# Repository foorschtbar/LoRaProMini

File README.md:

# LoRaProMini - A low power LoRaWAN Node

[

](https://github.com/foorschtbar/LoRaProMini)

A LoRaWAN sensor node, based on ATmega328P MCU (Arduino Pro Mini) and RFM95W/SX1276 LoRa Transceiver.

The module can be used:

- Collect various climate values with environmental sensors. See [Environmental (Weather/Clima) Sensor](#environmental-weatherclima-sensor)
- Tell if the letter carrier has put new letters in your mailbox. See [Mailbox Monitor](#mailbox-monitor)
- Notify if someone rang the doorbell
- Act a wirless button
- and many more...

## Features

- Deep sleep MCU and sensors between data transmissions
- Two interrupt inputs could use to wake up the MCU and sensors from deep sleep
- Confirmend und unconfirmend data up messages
- Ultra low power consumption. Under 10μA with all features and sensors
- Power input 3.5-6V:
  - Battery (Li-Ion or Li-SOCl2 works fine)
  - Battery with solar charger
- Sensor support
  - Bosch BME280 (humidity, barometric pressure and ambient temperature)
  - Maxim DS18B20(+)/DS18S20(+)/DS1822 1-Wire temperature sensor

### Warning

LoRaProMini does not take care of the compliance with the duty cycle limitation. Please select only transmission intervals that are within the legal limits (1%/0.1%). Please also note that the interrupt inputs may cause additional transmissions if this function is activated.

### PCB Ordering

:point_up: I still have a few PCBs left. If you are interested please contact me. Contact details can be found here: https://github.com/foorschtbar or visit my Tindie store:

## Example Applications

### Environmental (Weather/Clima) Sensor

- Download [Radiation Shield STL](https://www.prusaprinters.org/prints/73421-radiation-shield-for-diy-weather-station)
- Buy [Waterproof LED Solar Light](https://s.click.aliexpress.com/e/_9AKunB)

### Mailbox Monitor

- Download [Case STL](https://www.prusaprinters.org/prints/132941-case-for-lorawan-mailbox-monitor-lorapromini)
- Buy [Normally Opened Reed Switches](https://s.click.aliexpress.com/e/_AU1hN3)

## More pics

## The Things Stack configuration

- LoRaWAN version `MAC V1.0.3`

## How to use

1. Manufacture the PCB. Here you find the [Gerber](pcb) files
1. Assemble the PCB. Here you find the [Bill of Materials](https://foorschtbar.github.io/LoRaProMini/pcb/bom/ibom.html) (BOM)
   - **Attention:** The current version (v3.1) of the PCB has no ISP header! A pre-burned Atmega328P must be installed. I got one from an Arduino Pro Mini Board (3.3V 8 Mhz), because a completely assembled Arduino is cheaper than a single chip
1. Flash config firmware (See [How to flash](#how-to-flash))
1. Start voltage calibration from menu
1. Start configuration builder [Configuration Builder](https://foorschtbar.github.io/LoRaProMini/configbuilder)
1. Measure the voltage with a multimeter
1. Insert multimeter voltage and the analog value in the Volts-per-bit (VPB) calculator to get VPB factor.
1. If u have a adjustable power supply, try different voltages to find best factor. Warning: The maximum voltage is 6 Volt
1. Fill out the other fields like activation methode, session keys and EUIs
1. Write configuration to EEPROM using configuration menu
1. Check written configuration via configuration menu
1. Flash debug or release firmware (See [How to flash](#how-to-flash))
1. Finish

## How to flash

```
avrdude-F -v -c arduino -p atmega328p -P <COM PORT> -b 57600 -D -U flash:w:<FIRMWARE FILE>:i
```

Example:

```
avrdude -F -v -c arduino -p atmega328p -P COM4 -b 57600 -D -U flash:w:firmware_1.0_config.hex:i
```

## Firmware Changelog

### Version 2.7

- Fixed a problem of resetting the interrupt trigger too early.

### Version 2.6

- Second attempt to solve the unnecessary delay due to the duty cycle limitation. Overflow of timer0 freezes the MCU after around 20 transmissions.

### Version 2.5

- Fixed problem with duty cycle limitation
- Fixed MCU deepsleep inaccuracy

### Version 2.4

- An external interrupt during a transmission terminates the transmission and starts a new transmission.
- Enabled Link Check Mode

### Version 2.3

- Fixed Typo

### Version 2.2

- An additional send delay between 0 and 20s has been added to avoid overlaps between different nodes with exactly the same send interval
- Some flash memory optimizations

### Version 2.1

- Improved (debug) logging to serial output
- BME sends -127°C (link DS18x) if no sensor was found

### Version 2.0

- Added wake up trough interrupt pins
- Added option for disable interrupt pins
- Added option for confirmed uplink
- Changed LoRaWAN data up message
  - Added state of interrupt pins
  - Combined major and minor version byte into a single byte (4 bits for major and 4 bits for minor)

### Version 1.1

- Only for testing CI Pipeline

### Version 1.0

- Initial Version

## PCB Changelog

### Version 3.2

- Fixed C7 (Replaced 10uF with 100nF)

### Version 3.1

- Added white field to specify the Node ID

### Version 3.0

- Removed Arduino Pro Mini Dauther PCB
- Added ATMEGA328P direct to the PCB
- Added pins for unused GPIOs
- Added D2 and D3 with Pulldowns and connector as external interrupts (need FW v2.0 or higher)

### Version 2.2

- Added RST pin to connector for programming

### Version 2.1

- Added connector for programming

### Version 2.0

- Smaller PCB
- Rounded Edges
- Fixed issue with DS18x onboard pin mapping

### Version 1.0

- Initial PCB

## TTS Payload Formatter (formerly TTN Payload Decoder)

```javascript
function decodeUplink(input) {
  var bytes = input.bytes;

  var itrTrigger = (bytes[0] & 0x1) !== 0; // Message was triggered from interrupt (bit 0)
  var itr0 = (bytes[0] & 0x2) !== 0; // Interrupt 0 (bit 1)
  var itr1 = (bytes[0] & 0x4) !== 0; // Interrupt 1 (bit 2)
  var bat = (bytes[1] << 8) | bytes[2]; // Battery
  var fwversion = (bytes[3] >> 4) + "." + (bytes[3] & 0xf); // Firmware version
  var temp1 = (bytes[4] & 0x80 ? 0xffff << 16 : 0) | (bytes[4] << 8) | bytes[5]; // BME Temperature
  var humi1 = (bytes[6] << 8) | bytes[7]; // BME Humidity
  var press1 = (bytes[8] << 8) | bytes[9]; // BME Pressure
  var temp2 =
    (bytes[10] & 0x80 ? 0xffff << 16 : 0) | (bytes[10] << 8) | bytes[11]; // DS18x Temperature

  var mbStatus = "UNKNOWN";
  if (itr0) {
    mbStatus = "FULL";
  } else if (itr1) {
    mbStatus = "EMPTY";
  }

  return {
    data: {
      interrupts: {
        itr0: itr0,
        itr1: itr1,
        itrTrigger: itrTrigger,
      },
      extra: {
        mbStatus: mbStatus,
        mbChanged: itrTrigger,
      },
      fwversion: fwversion,
      bme: {
        temperature: temp1 / 100,
        humidity: humi1 / 100,
        pressure: press1,
      },
      ds18x: {
        temperature: temp2 / 100,
      },
      battery: bat / 100,
    },
    warnings: [],
    errors: [],
  };
}
```

## ToDo

- [ ] Go to sleep immediately when voltage is too low
- [ ] Multi point calibration for battery voltage
- [ ] Set ADR (On/Off)
- [ ] Set SF (7-12)
- [ ] Allow change of NetID
- [x] Add wake up trough interrupt pins
- [x] Move Major- and Minorversion byte to single byte. 4 bits for major and 4 bits for minor.
- [x] Add option for Confirmed Uplink to config
- [x] Add CI/CD pipeline to build firmware
- [x] Rewirte VBP calculator in Configuration Builder
- [x] Move config to EEPROM
- [x] Added special firmware to change configs
- [x] Build HTML/JS Interface to build configs
- [x] Add CRC32 check
- [x] Test ABP
- [x] Test OTAA
- [x] Deploy config tool via GitHub Pages
- [x] Fix problem when checksum in pastend config had zeros O.o
- [x] Add random EUI generator button to config tool
- [x] Parse config string to GUI fields

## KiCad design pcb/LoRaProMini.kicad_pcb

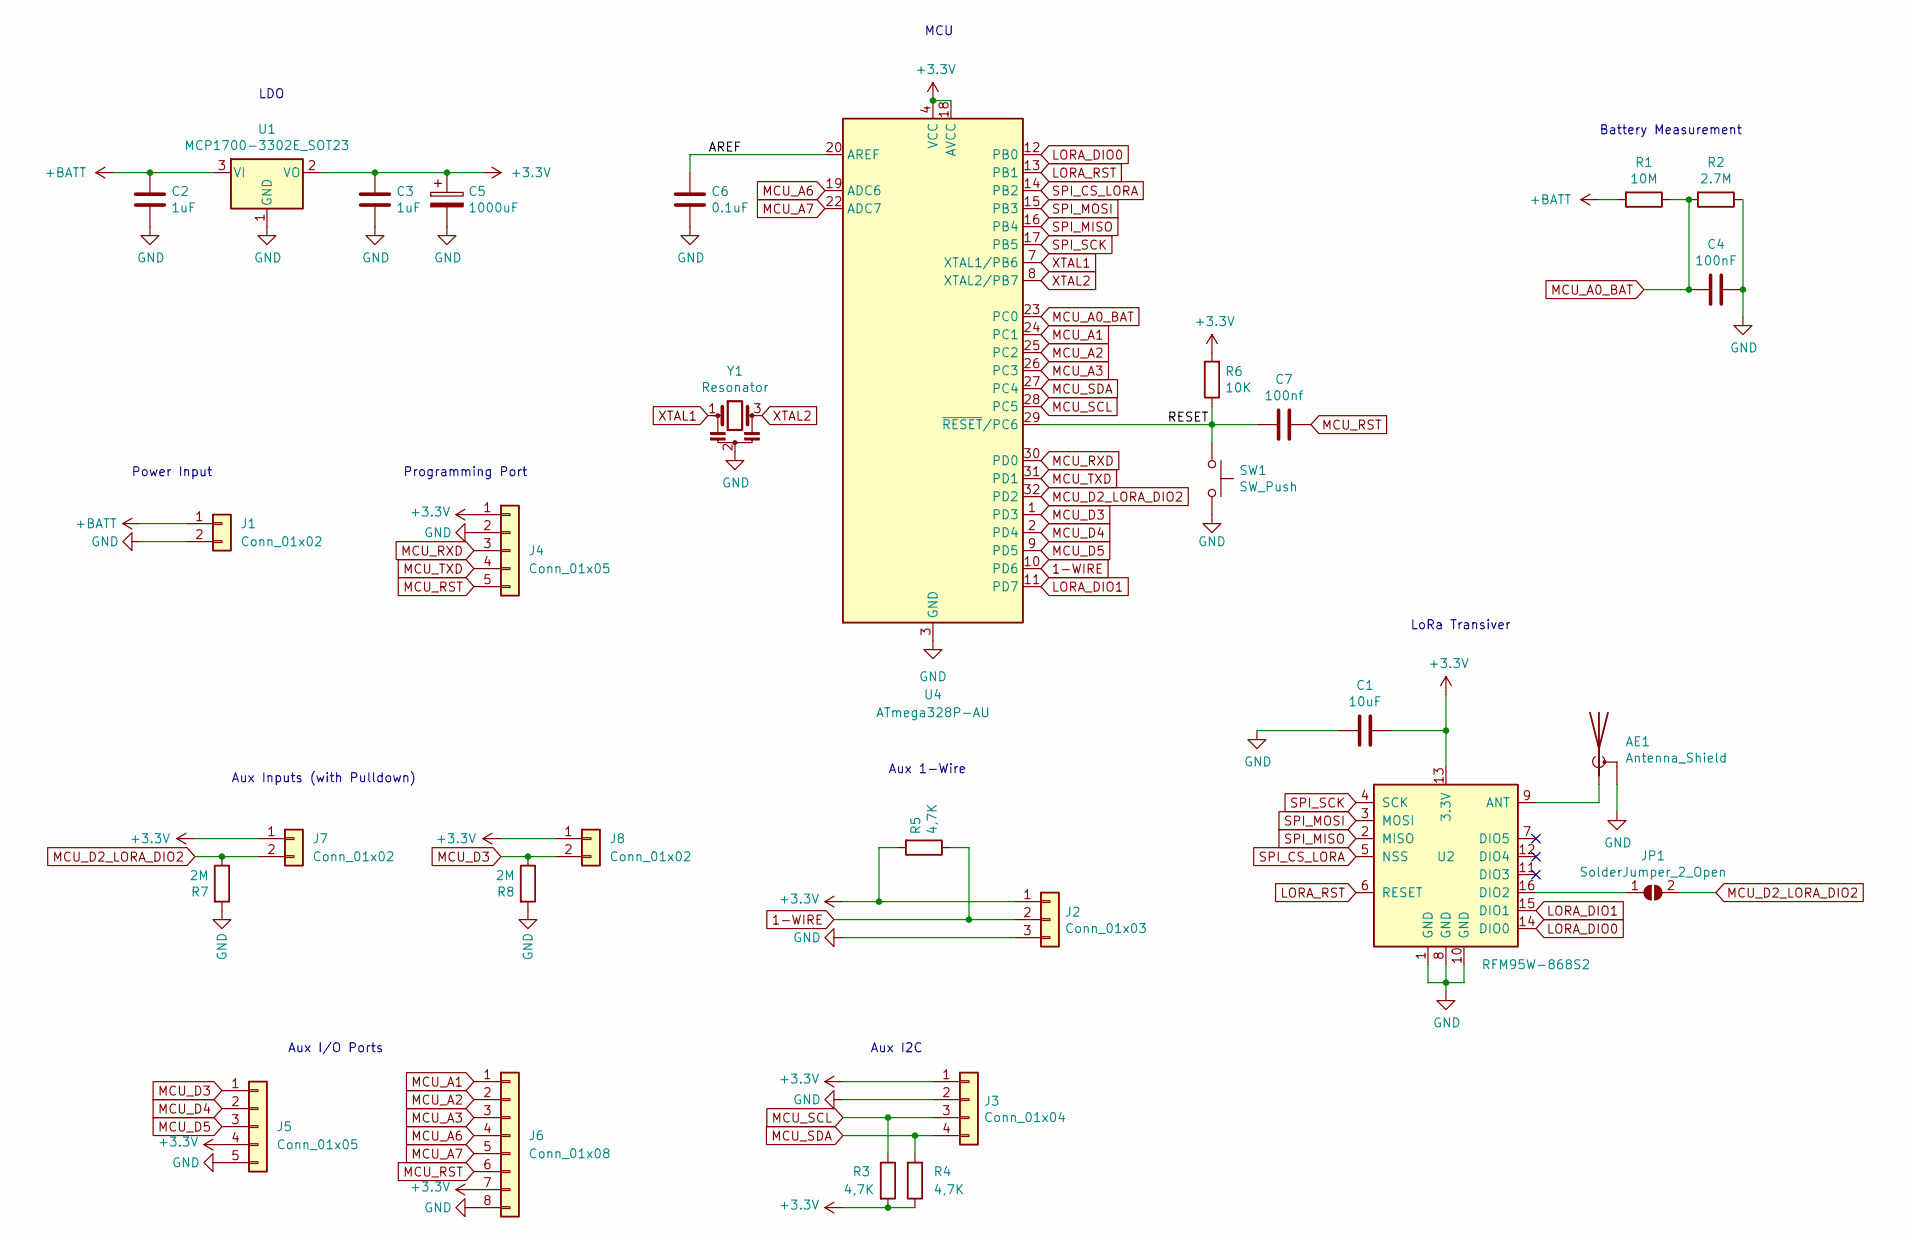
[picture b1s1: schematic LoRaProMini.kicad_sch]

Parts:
AE1: Antenna_Shield; Antenna_SMA_uFL
C1: 10uF; C_0805_2012Metric_Pad1.18x1.45mm_HandSolder
C2, C3: 1uF; C_0805_2012Metric_Pad1.18x1.45mm_HandSolder
C4: 100nF; C_0805_2012Metric_Pad1.18x1.45mm_HandSolder
C5: 1000uF; CP_EIA-7343-43_Kemet-X_Pad2.25x2.55mm_HandSolder
C6: 0.1uF; C_0805_2012Metric_Pad1.18x1.45mm_HandSolder
C7: 100nf; C_0805_2012Metric_Pad1.18x1.45mm_HandSolder
J1, J7, J8: Conn_01x02; JST_PH_B2B-PH-K_1x02_P2.00mm_Vertical
J2: Conn_01x03; JST_PH_B3B-PH-K_1x03_P2.00mm_Vertical
J3: Conn_01x04; JST_PH_B4B-PH-K_1x04_P2.00mm_Vertical
J4: Conn_01x05; PinHeader_1x05_P2.54mm_Vertical
J5: Conn_01x05; Holes_1x05_P2.54mm
J6: Conn_01x08; Holes_1x08_P2.54mm
JP1: SolderJumper_2_Open; SolderJumper-2_P1.3mm_Open_TrianglePad1.0x1.5mm
R1: 10M; R_0805_2012Metric_Pad1.20x1.40mm_HandSolder
R2: 2.7M; R_0805_2012Metric_Pad1.20x1.40mm_HandSolder
R3, R4, R5: 4,7K; R_0805_2012Metric_Pad1.20x1.40mm_HandSolder
R6: 10K; R_0805_2012Metric_Pad1.20x1.40mm_HandSolder
R7, R8: 2M; R_0805_2012Metric_Pad1.20x1.40mm_HandSolder
SW1: SW_Push; SW_SPST_CK_RS282G05A3
U1: MCP1700-3302E_SOT23; SOT-23
U2: RFM95W-868S2; HOPERF_RFM9XW_SMD
U4: ATmega328P-AU; TQFP-32_7x7mm_P0.8mm
Y1: Resonator; Resonator_SMD_Murata_CSTxExxV-3Pin_3.0x1.1mm

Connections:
1-WIRE: J2.2, R5.1, U4.10 (PD6)
+3.3V: C1.1, C3.1, C5.1, J2.1, J3.1, J4.1, J5.4, J6.7, J7.1, J8.1, R3.2, R4.1, R5.2, R6.2, U1.2 (VO), U2.13 (3.3V), U4.4 (VCC), U4.6 (VCC), U4.18 (AVCC)
+BATT: C2.1, J1.1, R1.2, U1.3 (VI)
/AREF: C6.1, U4.20 (AREF)
/RESET: C7.2, R6.1, SW1.1, U4.29 (~RESET/PC6)
GND: AE1.2 (Shield), C1.2, C2.2, C3.2, C4.1, C5.2, C6.2, J1.2, J2.3, J3.2, J4.2, J5.5, J6.8, R2.1, R7.2, R8.2, SW1.2, U1.1 (GND), U2.1 (GND), U2.8 (GND), U2.10 (GND), U4.3 (GND), U4.5 (GND), U4.21 (GND), Y1.2
LORA_DIO0: U2.14 (DIO0), U4.12 (PB0)
LORA_DIO1: U2.15 (DIO1), U4.11 (PD7)
LORA_RST: U2.6 (RESET), U4.13 (PB1)
MCU_A0_BAT: C4.2, R1.1, R2.2, U4.23 (PC0)
MCU_A1: J6.1, U4.24 (PC1)
MCU_A2: J6.2, U4.25 (PC2)
MCU_A3: J6.3, U4.26 (PC3)
MCU_A6: J6.4, U4.19 (ADC6)
MCU_A7: J6.5, U4.22 (ADC7)
MCU_D2_LORA_DIO2: J7.2, JP1.2 (B), R7.1, U4.32 (PD2)
MCU_D3: J5.1, J8.2, R8.1, U4.1 (PD3)
MCU_D4: J5.2, U4.2 (PD4)
MCU_D5: J5.3, U4.9 (PD5)
MCU_RST: C7.1, J4.5, J6.6
MCU_RXD: J4.3, U4.30 (PD0)
MCU_SCL: J3.3, R3.1, U4.28 (PC5)
MCU_SDA: J3.4, R4.2, U4.27 (PC4)
MCU_TXD: J4.4, U4.31 (PD1)
unnamed: AE1.1 (A), U2.9 (ANT)
unnamed: JP1.1 (A), U2.16 (DIO2)
SPI_CS_LORA: U2.5 (NSS), U4.14 (PB2)
SPI_MISO: U2.2 (MISO), U4.16 (PB4)
SPI_MOSI: U2.3 (MOSI), U4.15 (PB3)
SPI_SCK: U2.4 (SCK), U4.17 (PB5)
XTAL1: U4.7 (XTAL1/PB6), Y1.1
XTAL2: U4.8 (XTAL2/PB7), Y1.3

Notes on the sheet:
Aux 1-Wire
Aux I/O Ports
LDO
MCU
Power Input
Battery Measurement
Aux I2C
Aux Inputs (with Pulldown)
Programming Port
LoRa Transiver

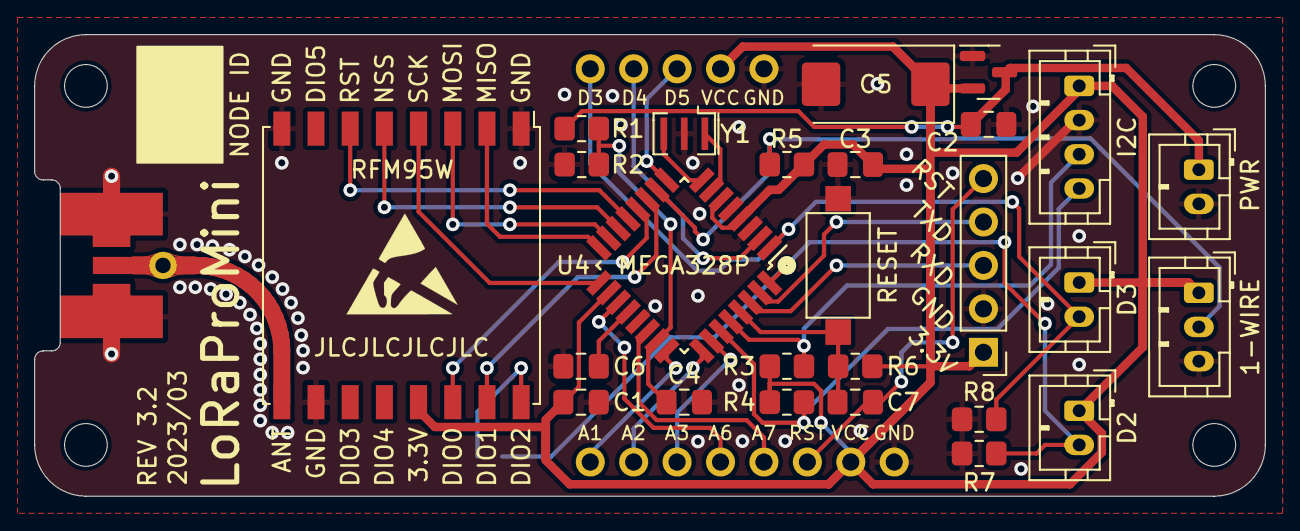
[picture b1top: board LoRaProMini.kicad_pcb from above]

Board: 2 copper layers, 72.0 x 27.0 mm, 30 parts (1 on the bottom side), 32 nets.

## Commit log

2021-03-26 Added KiCad Project
2021-03-27 Fixed ProMini Pinout (SDA missing, A4/A5 position bad)
2021-03-27 Added LMIC docu and some datasheets
2021-03-27 Added sample config file
2021-03-27 Added ABP and OTAA activation method
2021-03-28 Added A6/A7 to Arduino Pro Mini Pinout
2021-03-28 Updated KiCad Project
2021-04-24 Added battery voltage measurement
2021-05-08 Added the first PCB Layout
2021-05-08 Added DS18B20 Datasheet
2021-05-08 Update PCB
2021-05-15 Added code for 1-Wire sensors
2021-05-16 Replaced DallasTemperature with a own, smaller library
2021-05-16 Added TinyBME to replace Adafruit BME library
2021-05-16 Added README to TinyDallas
2021-05-16 Optimized code for TinyBME and TinyDallas
2021-05-16 Added TTN payload decoder
2021-05-21 Removed fixed DS18B20 address. Now first found sensor will be used
2021-05-21 Added a Voltage Calibration Mode
2021-05-21 Added "continue sleep if voltage is to low" feature
2021-05-21 Added Datasheet for BME280
2021-05-21 Updated PCB
2021-05-22 Added Gerber files
2021-06-05 Fixed typo in platformio.ini
2021-06-05 Debug messages aligned
2021-06-05 Added REV 2.0 PCB
    - Resized PCB
    - Fixed DS18x orientation
2021-07-03 Added REV 2.1 PCB
2021-07-03 Added images to README
2021-07-05 Replaced REV 2.1 PCB
2021-07-11 Moved config to EEPROM
    - Added special firmware for change configuration
    - Added ToDos to README
    - Removed config.h
2021-07-11 Tested and fixed OTAA
    - and code cleanup
2021-07-11 Added HTML/JS Interface to build configs
2021-07-12 Some improvements for TTN v3
2021-07-15 Parse config string to GUI and generate EUI
2021-07-15 Remove unused variable
2021-07-16 Fixed problems with pasted config strings
2021-07-16 GitHub Pages Deploy
2021-07-16 Initial gh-pages commit
2021-07-16 Deploying to gh-pages from @ 4bd763b2cf0b29013262e6ce5401fd8d201e021e 🚀
2021-07-16 Deploying to gh-pages from @ cb1b14362f3a9417aab85358711ab35aa680ab96 🚀
2021-07-16 Updated README
    Added how to use section
2021-07-16 Added a fw version to payload
2021-07-16 Test CI/CD pipeline
2021-07-16 Bumped version to 1.0
2021-07-16 Merged CI scripts
2021-07-16 Unmerged CI scripts
2021-07-16 Added VBP calculator to configuration builder
2021-07-16 Deploying to gh-pages from @ abb99c573e9bbbe00a4c14da265d70854e3dc9f6 🚀
2021-07-17 Fixed typo
2021-07-17 Deploying to gh-pages from @ 3c30f07040eb4b4e9e958133b3f8575f35001df6 🚀
2021-08-31 Added RST Pin to Programmer Interface
2021-08-31 Added some documents for WIP without Pro Mini
2021-09-11 Improved configuration builder field labels
2021-09-11 Deploying to gh-pages from @ 8de83f1b052ac41eb7d67e39079a12df76c33b44 🚀
2021-09-11 Deploying to gh-pages from @ efc8e57893b64fa294fc52ca679ae023a3542cc0 🚀
2021-09-11 Fixed GitHub Pages Deploy Action
2021-09-11 Deploying to gh-pages from @ foorschtbar/LoRaProMini@13a89ac0f6c5fc262e24570bd1a64cbb64207374 🚀
2021-09-20 Replaced Arduino Pro Mini Dauther PCB
    - Added ATmega328P direct to the PCB
    - Added pins for unsed GPIOs
    - Added D2 and D3 with Pulldown and connector as external Interrupts
2021-09-25 Update docu folder
2021-09-25 Added counters to debug messages
2021-09-25 Optimized debug messages
2021-09-25 Deploying to gh-pages from @ foorschtbar/LoRaProMini@318fc4ffa92ef16c5fedc29ff8cc4a630da75790 🚀
2021-09-25 Fixed link in readme
2021-09-25 Create LICENSE
2021-10-06 Added BOM
2021-10-06 Deploying to gh-pages from @ foorschtbar/LoRaProMini@bf128a1f834eec7f38ef12298e242dae39b3a8af 🚀
2021-10-06 Renamed pcb und docu folder
2021-10-06 Deploying to gh-pages from @ foorschtbar/LoRaProMini@c86ee87850962be65a721272836bd2499cfddaab 🚀
2021-10-07 Added new image
2021-10-07 Send -127°C if no BME sensor was found
2021-10-07 Deploying to gh-pages from @ foorschtbar/LoRaProMini@464e1e5ab72d56df852eeabe293f1c7ae37b73d2 🚀
2021-10-08 Added ISP header warning
2021-10-08 Deploying to gh-pages from @ foorschtbar/LoRaProMini@7a25ded7b8b728d73e9e39a2767dce27c2b57135 🚀
2021-10-14 Added white field to PCB to specify the Node ID
2021-10-14 Deploying to gh-pages from @ foorschtbar/LoRaProMini@a938d8310966b8f3c1edb3024db222770cf6ebb0 🚀
2021-10-15 Added random send delay
    - An additional send delay between 0 and 20s has been added to avoid overlaps between different nodes with exactly the same send interval
    - Some Flash memory optimizations
2021-10-15 Deploying to gh-pages from @ foorschtbar/LoRaProMini@2551214b192ca4ae097206c5551a830a10177cb6 🚀
2021-12-05 Added image and videos for Mailbox Monitor
2021-12-05 Deploying to gh-pages from @ foorschtbar/LoRaProMini@385ebb23d36a211085108cbabca7fee35ba48c5e 🚀
2021-12-22 Renamed Payload Decoder to Formatter
2021-12-23 Updated iBOM for PCB Rev 3.1
2021-12-23 Deploying to gh-pages from @ foorschtbar/LoRaProMini@53c212bf3b7de3939a467a577e88bfaa23f4570d 🚀
2021-12-24 Update iBOM
2021-12-29 Fixed Typos
2021-12-31 - Interrupt and ADR improvments
2022-01-10 Updated todos
2022-01-21 Refactor JS code
    Replaced function statements with function expressions/lambda expressions
2022-01-24 Refactor JS code
2022-02-12 Deploying to gh-pages from @ foorschtbar/LoRaProMini@5aacb4927cebe00147be36467089d95d9d84d021 🚀
2022-02-12 Deploying to gh-pages from @ foorschtbar/LoRaProMini@3c92a416975d42550d1d1b66df71636bba1685ab 🚀
2022-02-12 Deploying to gh-pages from @ foorschtbar/LoRaProMini@c23537d159f1eb8bcc9751f87a73fe5ab24b5212 🚀
2022-02-14 Fixed MCU deepsleep inaccuracy
2022-02-15 Fixed problem with duty cycle limitation
2022-02-15 Deploying to gh-pages from @ foorschtbar/LoRaProMini@e9d4a54a9425f6701069cd11a20a8df3336dca98 🚀
2022-02-19 Second attempt to solve the unnecessary delay due to the duty cycle limitation
2022-02-19 Re-extend debug messages
2022-02-19 Deploying to gh-pages from @ foorschtbar/LoRaProMini@c96a483469a960b660d8aa4cba11d23b62856b37 🚀
2022-04-03 Update README.md
    Fixed Typo
2022-04-03 Deploying to gh-pages from @ foorschtbar/LoRaProMini@5dd1e6b6f975296069abfd730d90300b2c3cd495 🚀
2022-04-10 Deploying to gh-pages from @ foorschtbar/LoRaProMini@a942423417fdefbadff50c50bfc1a3524a2f37b9 🚀
2022-05-09 bugfix: Reset state ItrTrigger after sending
2022-05-26 Fixed issue with Config Builder WebUI buttons
2022-05-26 Deploying to gh-pages from @ foorschtbar/LoRaProMini@50cc59d02df85ef451724bbe8b5012a2dbb1aeb3 🚀
2022-05-26 Renamed reset_itr_trigger_state function
2022-05-26 Deploying to gh-pages from @ foorschtbar/LoRaProMini@87c37cc2348dd26ffd6cb096ab2bfc78e52228e0 🚀
2023-03-20 Updated gitignore
2023-03-20 Removed KiCad V6 Files
2023-03-20 Added project based footprints
2023-03-20 Fixed C7 (10uf --> 100nF)
2023-03-20 Upgraded Gerbs to REV3.2
2023-03-20 Deploying to gh-pages from @ foorschtbar/LoRaProMini@dd729ec15837fde522fa1ca763856ea42da4f562 🚀
2023-03-21 Deploying to gh-pages from @ foorschtbar/LoRaProMini@65a1b30cdf68f3691e3546b1f50b6d625394b7ef 🚀
2024-02-29 Removes duplicated silkscreen from gerbers (fixes #4)
2024-04-20 Added Tindie store link
2024-04-20 Deploying to gh-pages from @ foorschtbar/LoRaProMini@056aaf14bbbe981b3dd102651f9e653f291c1346 🚀
2024-04-20 Deploying to gh-pages from @ foorschtbar/LoRaProMini@1e3428f3a4a409d2a3c9f284759b2620453ed363 🚀

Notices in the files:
pcb/LoRaProMini.kicad_pcb:
(c) 2023 foorschtbar
© 2021 foorschtbar
